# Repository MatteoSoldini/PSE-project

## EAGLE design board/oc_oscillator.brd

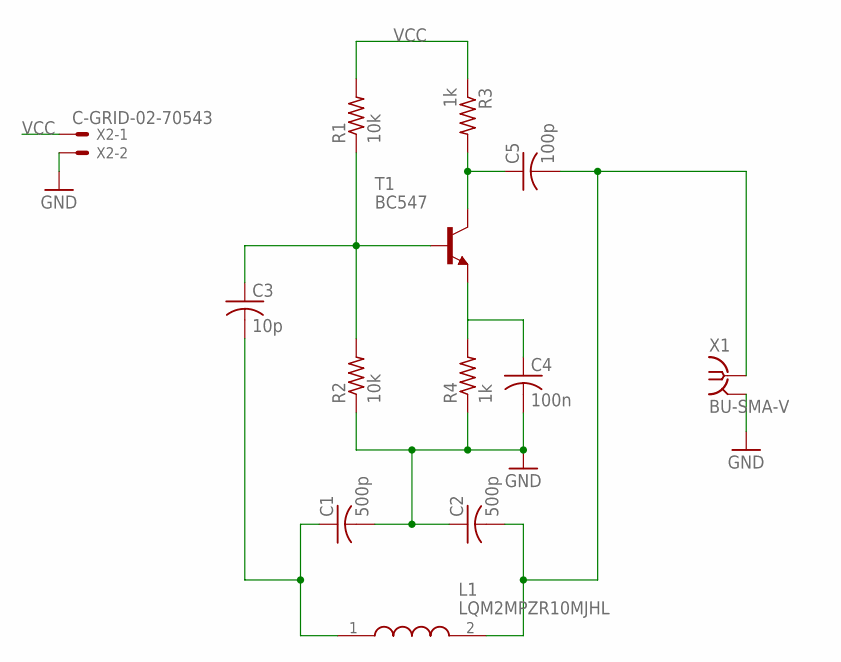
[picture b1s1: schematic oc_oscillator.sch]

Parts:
C1, C2: 500p; C0805
C3: 10p; C0805
C4: 100n; C0805
C5: 100p; C0805
L1: LQM2MPZR10MJHL; INDC2016X120N
R1, R2: 10k; M0805
R3, R4: 1k; M0805
T1: BC547; TO92
X1: BU-SMA-V
X2: C-GRID-02-70543; 70543-02

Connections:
GND: C1.2, C2.1, C4.2, R2.1, R4.1, X1.2, X1.3 (2), X1.4 (2), X1.5 (2), X2.2
unnamed: C4.1, R4.2, T1.1 (E)
unnamed: C5.1, R3.2, T1.3 (C)
unnamed: C3.1, R1.1, R2.2, T1.2 (B)
unnamed: C1.1, C3.2, L1.1
unnamed: C2.2, C5.2, L1.2, X1.1
VCC: R1.2, R3.1, X2.1

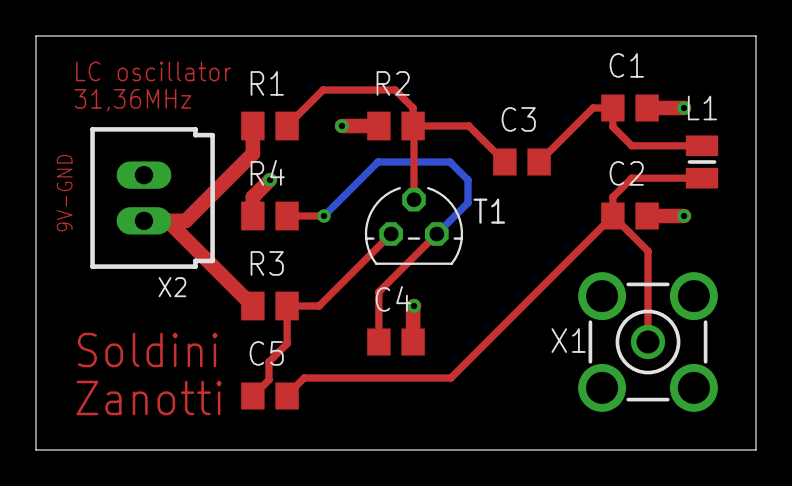
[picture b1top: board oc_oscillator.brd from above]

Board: 2 copper layers, 40.0 x 23.0 mm, 13 parts (0 on the bottom side), 7 nets.

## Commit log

2023-05-22 Add ideal rc oscillator
2023-05-22 🐛 Buggy
2023-05-25 🔥 Add lc oscillator
2023-05-25 🔧 Fix rc oscillators
2023-05-25 📈 Add chart for ideal and real oscillator
2023-05-31 Add not working hartley oscillator
2023-06-01 add more not working oscillators
2023-06-01 Add 555 oscillator
2023-06-01 fix lc oscillators
2023-06-01 Add 555 oscillator screenshot
2023-06-06 Fix hartley oscillator
2023-06-06 fix colpitts oscillator
2023-06-06 working lc oscillators
2023-06-07 Add screenshot LC
2023-06-12 Add board
2023-06-12 add board image & gerber
2023-06-13 ✏️ Add 9v label to board
